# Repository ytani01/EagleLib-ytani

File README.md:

# EagleLib-ytani -- EAGLE Libraries and some examples

既製品のモジュール基板を使う場合、
Eagleライブラリに部品がなく、
探しても見つからなかったり、
見つかってもどうもしっくりこないものが多く、
歯がゆい思いをしてたので、自分が使いやすいパーツライブラリを作ることにしました。

* Amazonなどのリンク情報も入れました。
* 秋月電子の通販コードも入れました。
* 裏返しで使うことがあるものは、裏のパターンも作りました。

まだまだ、少ないですが、徐々に増やしていきたいと思います。

## Install Library files

### 1. Clone git repository

```bash
$ git clone https://www.github.com/ytani01/EagleLib.git
```
or 
```bash
$ git clone git@github.com:ytani01/EagleLib.git
```

### 2. Make destination folder

Destination Folder:
```
C:\Users\{username}\Documents\EAGLE\libraries\ytani
```

### 3. Copy library files to destination folder

Source files: 
```
lib/*
```

### 4. Update on Eagle

1. [Control Panel]-[Libraries]-[libraries]-[ytani]-[*.lbr]
2. Right-click menu
3. [Update]

## [Libraries](lib/)

* ytani1.lbr

## How To

### common

#### Grid

Size: 1.27 mm
Multiple: 2

### Footprint

### Symbol

### Device

## Apendix.

### A.1 [examples](example/)

* [Raspberry Pi Zero HAT](example/RPi0-HAT1/)
* [Raspberry Pi Zero Power Module 1](example/RPi0PWR1/)
* [Raspberry Pi Zero Power Module 2](example/RPi0PWR2/)

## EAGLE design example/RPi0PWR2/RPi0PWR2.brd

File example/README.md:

# Examples

* [Raspberry Pi Zero HAT](RPi0-HAT1/)
* [Raspberry Pi Zero Power Module](RPi0PWR/)

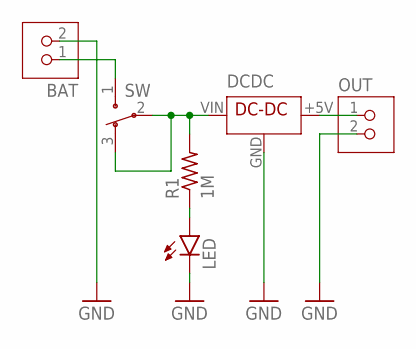
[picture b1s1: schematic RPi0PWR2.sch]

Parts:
BAT: JST-PH2
DCDC: DCDC-5V-0.48A
LED: LED3MM
OUT: JST-PH2
R1: 1M; 0204/5
SW: SW3-1

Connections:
BAT+: DCDC.VIN, R1.2, SW.2, SW.3
GND: BAT.2, DCDC.GND, LED.K (C), OUT.2
LED+: LED.A, R1.1
unnamed: DCDC.+5V (VOUT), OUT.1
unnamed: BAT.1, SW.1

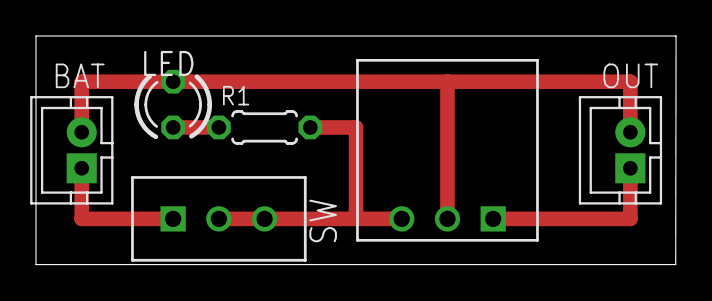
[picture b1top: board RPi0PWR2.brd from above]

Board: 2 copper layers, 35.6 x 12.7 mm, 6 parts (0 on the bottom side), 5 nets.

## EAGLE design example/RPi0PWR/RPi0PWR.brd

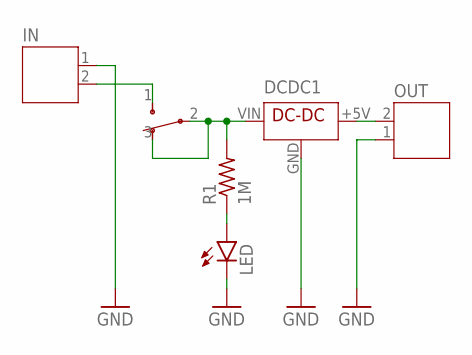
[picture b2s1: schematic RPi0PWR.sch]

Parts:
DCDC1: +5V; DC-DC_5V_0.48A
IN: JST-PH2
LED: LED3MM
OUT: JST-PH2
R1: 1M; 0204/5
SW1: SW3-1

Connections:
+5V: DCDC1.+5V (VOUT), OUT.2
BAT+: DCDC1.VIN, R1.2, SW1.2, SW1.3
BAT+0: IN.2, SW1.1
GND: DCDC1.GND, IN.1, LED.K (C), OUT.1
LED+: LED.A, R1.1

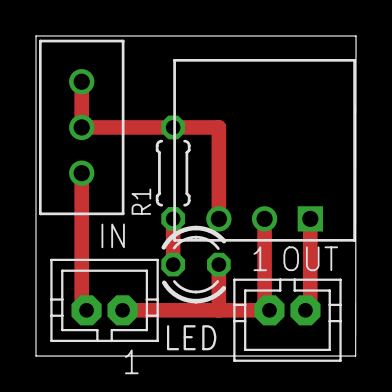
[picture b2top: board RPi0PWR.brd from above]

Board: 2 copper layers, 17.8 x 17.8 mm, 6 parts (0 on the bottom side), 5 nets.

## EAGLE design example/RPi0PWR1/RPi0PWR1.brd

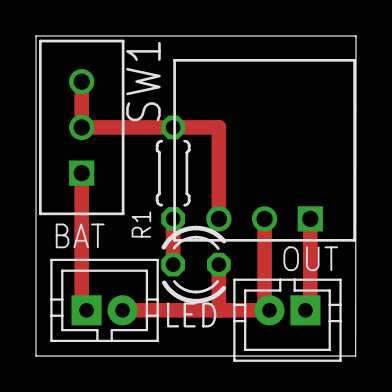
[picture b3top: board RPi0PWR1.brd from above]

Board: 2 copper layers, 17.8 x 17.8 mm, 6 parts (0 on the bottom side), 5 nets.

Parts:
BAT: JST-PH2
DCDC1: DCDC-5V-0.48A
LED: LED3MM
OUT: JST-PH2
R1: 1M; 0204/5
SW1: SW3-1

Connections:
BAT+: DCDC1.VIN, R1.2, SW1.2, SW1.3
GND: BAT.2, DCDC1.GND, LED.K, OUT.2
LED+: LED.A, R1.1
unnamed: DCDC1.+5V, OUT.1
unnamed: BAT.1, SW1.1

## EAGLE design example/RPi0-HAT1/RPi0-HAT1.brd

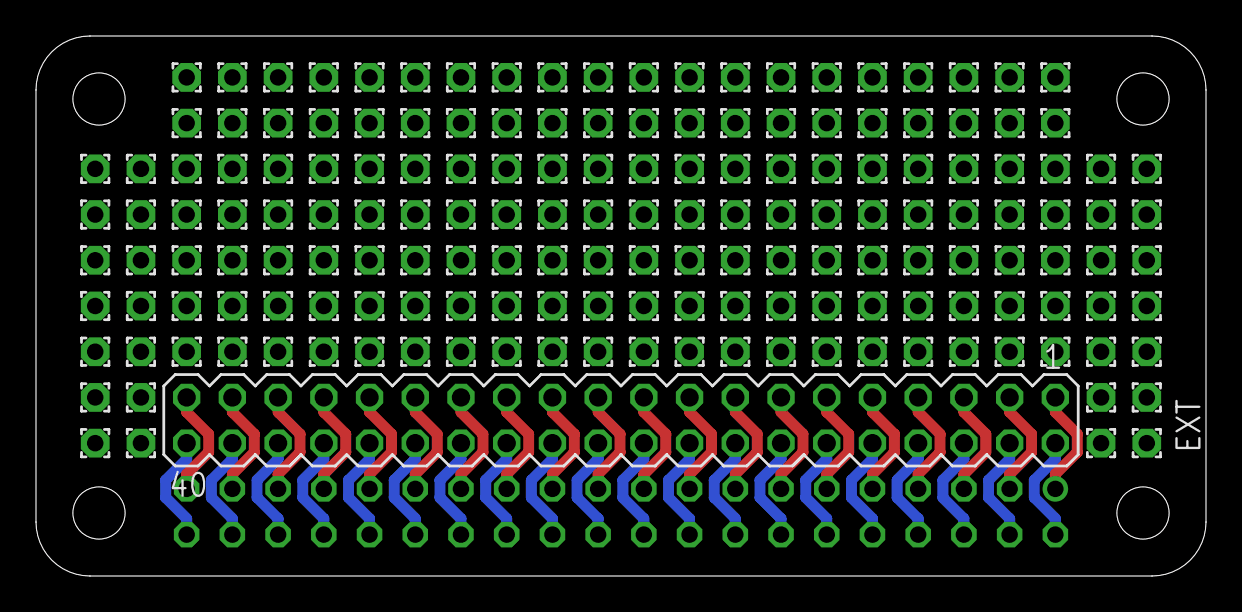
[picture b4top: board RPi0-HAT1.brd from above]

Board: 2 copper layers, 65.0 x 30.0 mm, 170 parts (1 on the bottom side), 40 nets.

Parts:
EXT: MA20-2
PAD1, PAD2, PAD3, PAD4, PAD5, PAD6, PAD7, PAD8, PAD9, PAD10, PAD11, PAD12, PAD13, PAD14, PAD15, PAD16, PAD17, PAD18, PAD19, PAD20, PAD21, PAD22, PAD23, PAD24, PAD25, PAD26, PAD27, PAD28, PAD29, PAD30, PAD31, PAD32, PAD33, PAD34, PAD35, PAD36, PAD37, PAD38, PAD39, PAD40, PAD41, PAD42, PAD43, PAD44, PAD45, PAD46, PAD47, PAD48, PAD49, PAD50, PAD51, PAD52, PAD53, PAD54, PAD55, PAD56, PAD57, PAD58, PAD59, PAD100, PAD101, PAD102, PAD103, PAD104, PAD105, PAD106, PAD107, PAD108, PAD109, PAD110, PAD111, PAD112, PAD113, PAD114, PAD115, PAD116, PAD117, PAD118, PAD119, PAD120, PAD121, PAD122, PAD123, PAD124, PAD125, PAD126, PAD127, PAD128, PAD129, PAD130, PAD131, PAD132, PAD133, PAD134, PAD135, PAD136, PAD137, PAD138, PAD139, PAD140, PAD141, PAD142, PAD143, PAD144, PAD145, PAD146, PAD147, PAD148, PAD150, PAD151, PAD152, PAD153, PAD154, PAD155, PAD156, PAD157, PAD158, PAD159, PAD160, PAD161, PAD162, PAD164, PAD165, PAD166, PAD167, PAD168, PAD169, PAD170, PAD171, PAD172, PAD173, PAD174, PAD175, PAD176, PAD179, PAD180, PAD181, PAD182, PAD183, PAD184, PAD185, PAD186, PAD187, PAD188, PAD189, PAD190, PAD191, PAD192, PAD193, PAD194, PAD195, PAD196, PAD201, PAD202, PAD203, PAD205, PAD206, PAD207, PAD208, PAD209, PAD210, PAD211, PAD212, PAD213, PAD214, PAD216, PAD217, PAD218: 1,6/0,9
RPI: FE20-2

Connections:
unnamed: EXT.2, RPI.2
unnamed: EXT.4, RPI.4
unnamed: EXT.6, RPI.6
unnamed: EXT.8, RPI.8
unnamed: EXT.10, RPI.10
unnamed: EXT.12, RPI.12
unnamed: EXT.14, RPI.14
unnamed: EXT.16, RPI.16
unnamed: EXT.18, RPI.18
unnamed: EXT.20, RPI.20
unnamed: EXT.22, RPI.22
unnamed: EXT.24, RPI.24
unnamed: EXT.26, RPI.26
unnamed: EXT.28, RPI.28
unnamed: EXT.30, RPI.30
unnamed: EXT.32, RPI.32
unnamed: EXT.34, RPI.34
unnamed: EXT.36, RPI.36
unnamed: EXT.38, RPI.38
unnamed: EXT.40, RPI.40
unnamed: EXT.1, RPI.1
unnamed: EXT.3, RPI.3
unnamed: EXT.5, RPI.5
unnamed: EXT.7, RPI.7
unnamed: EXT.9, RPI.9
unnamed: EXT.11, RPI.11
unnamed: EXT.13, RPI.13
unnamed: EXT.15, RPI.15
unnamed: EXT.39, RPI.39
unnamed: EXT.37, RPI.37
unnamed: EXT.35, RPI.35
unnamed: EXT.33, RPI.33
unnamed: EXT.31, RPI.31
unnamed: EXT.29, RPI.29
unnamed: EXT.27, RPI.27
unnamed: EXT.25, RPI.25
unnamed: EXT.23, RPI.23
unnamed: EXT.21, RPI.21
unnamed: EXT.19, RPI.19
unnamed: EXT.17, RPI.17

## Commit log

2020-09-14 init
2020-09-14 README.md
2020-09-15 SW3-1
2021-02-21 [add] ESP-32S
2021-02-21 [fix] DC-DC
2021-03-16 TP4056MOD2-TYPE-C
2021-07-10 Add: UART CH340G
2021-07-11 Add: YIC ZTT
2021-07-23 Add: LOLIN D32
2021-09-21 ADD: DCDC-SX1308-MOD1
2021-09-26 ADD: ADC MCP3425
2021-09-30 ADD: MOS FET 2SK4017
2021-11-18 ADD: M5StampPico
2021-11-29 ADD: M5Stamp Pico SMD
2021-12-20 ADD: ATTiny85
2021-12-20 UPD: ATTiny85
2022-01-16 ADD: LOGO
2022-03-26 USB-C-DIRECT
2022-03-28 USB-C-
2022-05-27 ADD: AE-USB2.0-TYPE-C-CTRPB-1
2022-10-09 ADD: SK6812MINI-E
2022-10-16 UPD: SK6812MINI-E
2022-10-16 ADD: PAD
2022-11-09 ADD:
2022-11-09 UPD: BAT-CR2032, PAD
2022-11-11 ADD: WS2812B
2022-11-17 UPD:
2022-12-29 ADD: CR-2032 and Logo
2023-06-10 UPD: SK6812MINI-E, CR-2032
